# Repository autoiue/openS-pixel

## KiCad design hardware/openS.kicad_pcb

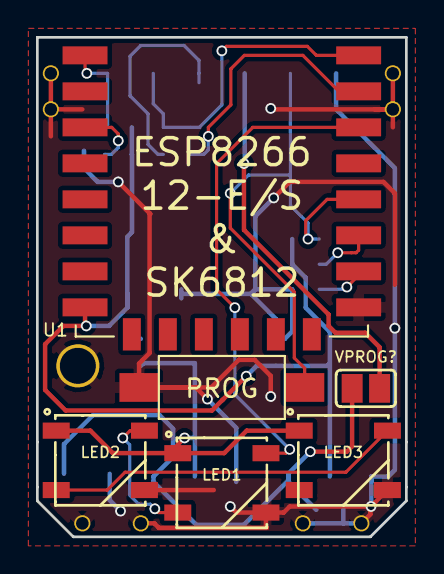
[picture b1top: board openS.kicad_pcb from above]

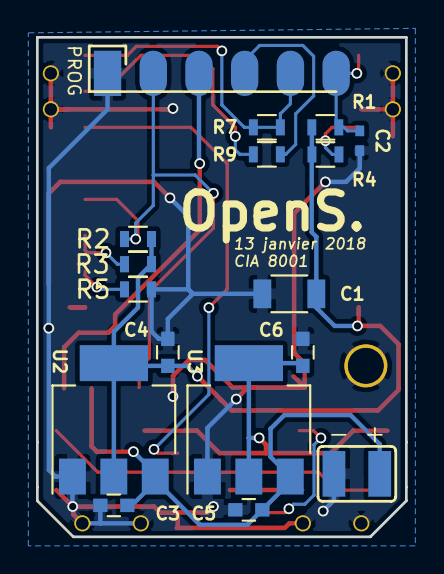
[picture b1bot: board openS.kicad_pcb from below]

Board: 2 copper layers, 20.5 x 27.8 mm, 23 parts (17 on the bottom side), 16 nets.

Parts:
C1: 100µF; C_1206
C2: 470pF (0603); C_0402_NoSilk
C3, C5: 1µF; C_0603
C4, C6: 10µF; C_0603
J2: NodeMCU Reset FTDI Header; FTDI_Header
J4: 9V; SJ_WIDE
JP1: VFTDI; SJ_OPEN
LED1, LED2, LED3: SK6812; WS2812B
R1, R2, R3, R4, R5: 12k; R_0603
R7: 0; R_0603
R9: 470; R_0603
SW1: PROG; SW_SPST_TE_ALCO_1437566
U1: ESP-12E
U2: TLV1117-33; SOT-223-3_TabPin2
U3: LD1117S50TR_SOT223; SOT-223-3_TabPin2

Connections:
+3V3: C1.1, C4.1, R1.1, R2.1, R3.1, R4.1, U1.8, U2.2
+5V: C6.1, LED1.1, LED2.1, LED3.1, U3.2
+9V: C3.1, C5.1, J4.1, JP1.1, U2.3, U3.3
/EN: R4.2, U1.3
/FTRX: J2.5, R7.1, R7.2, U1.16
/FTTX: J2.4, R9.1
/GPIO0: J2.2, R2.2, SW1.1, U1.12
/GPIO2: R3.2, U1.11
/GPIO15: R5.2, U1.10
/REST: C2.1, J2.6, R1.2, U1.1
/RX: R9.2, U1.15
/SK_OUT: LED1.4, U1.14
/VCC: J2.3, JP1.2
GND: C1.2, C2.2, C3.2, C4.2, C5.2, C6.2, J2.1, J4.2, LED1.3, LED2.3, LED3.3, R5.1, SW1.2, U1.9, U2.1, U3.1
unnamed: LED1.2, LED2.4
unnamed: LED2.2, LED3.4

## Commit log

2022-11-30 Archive OpenS
